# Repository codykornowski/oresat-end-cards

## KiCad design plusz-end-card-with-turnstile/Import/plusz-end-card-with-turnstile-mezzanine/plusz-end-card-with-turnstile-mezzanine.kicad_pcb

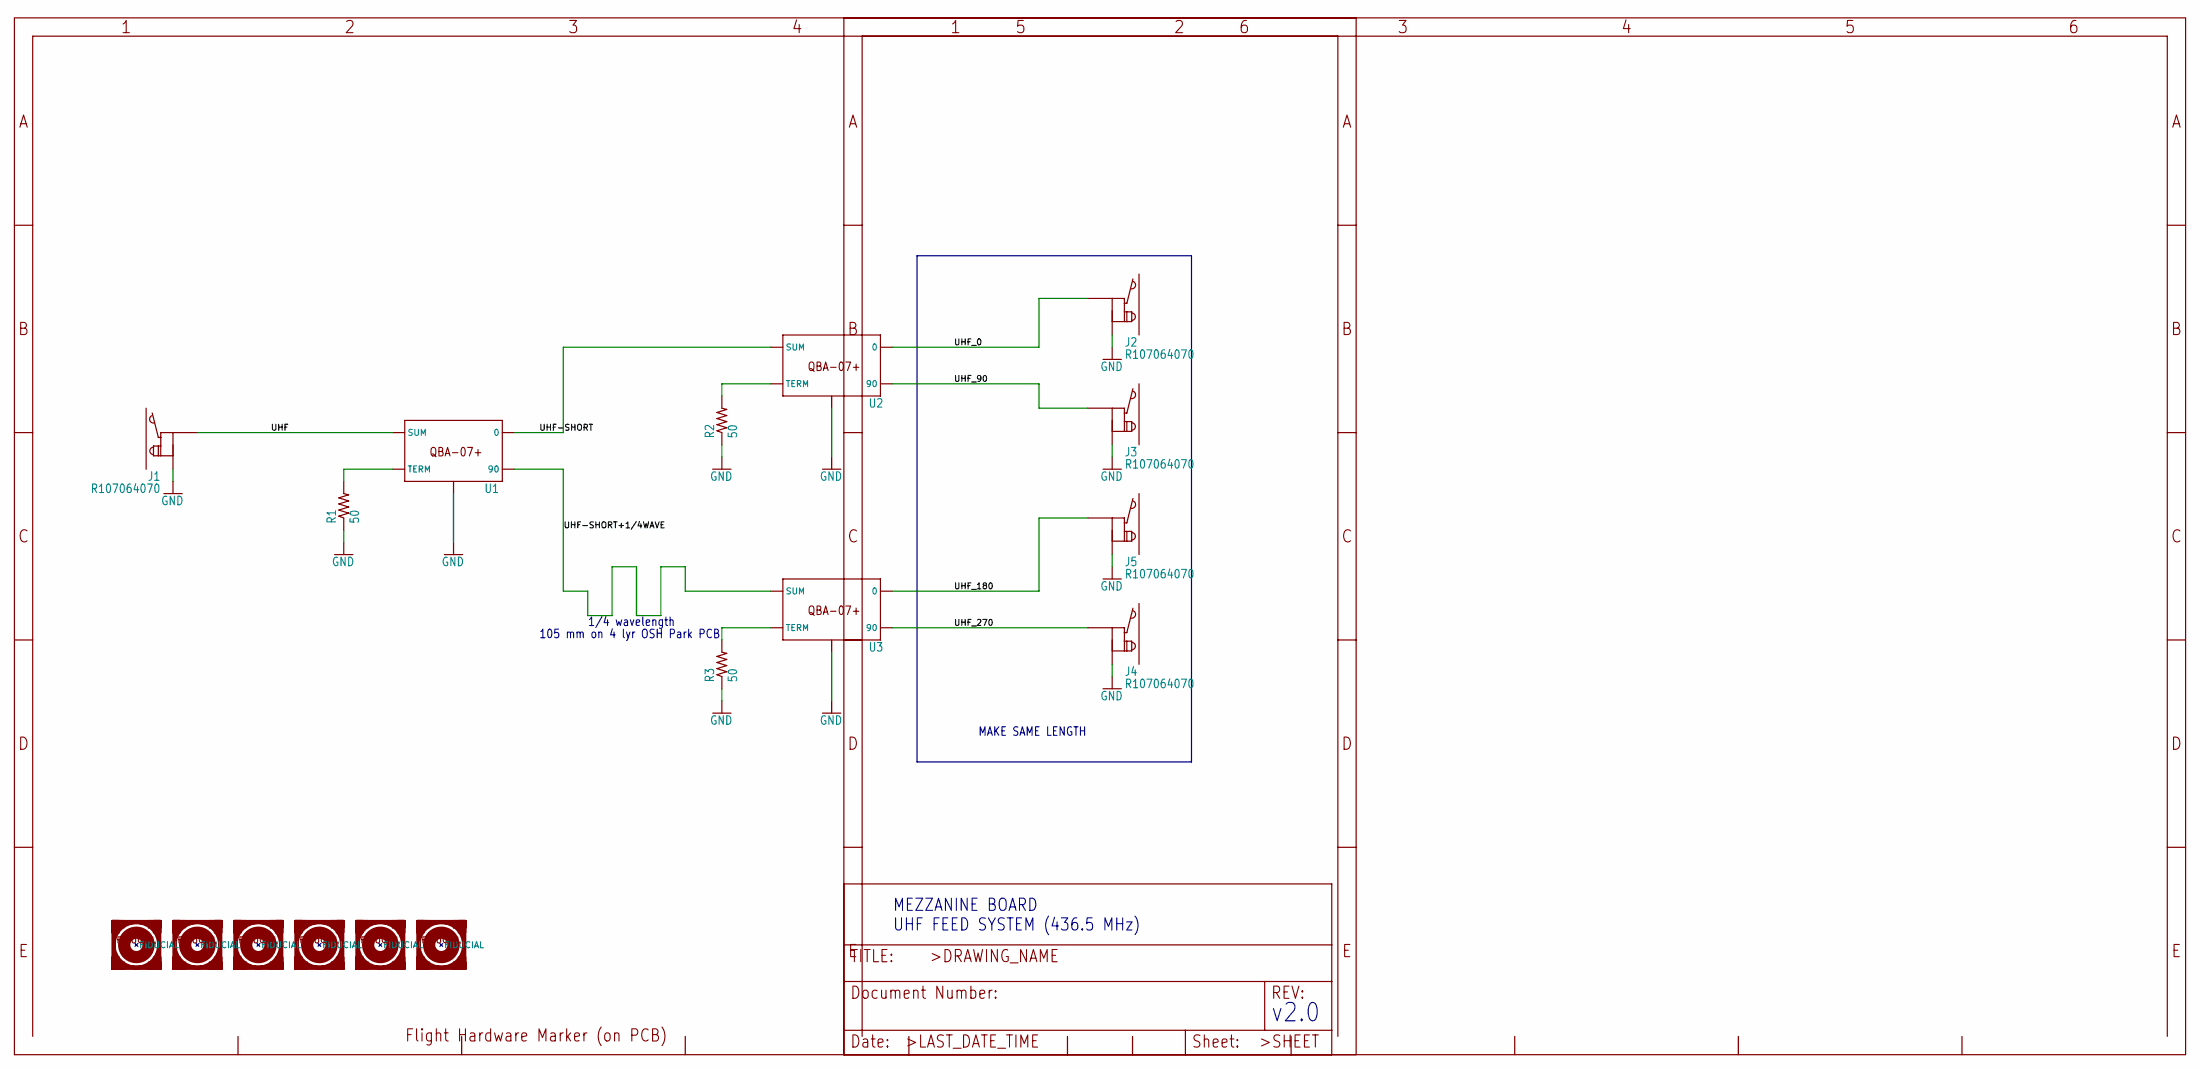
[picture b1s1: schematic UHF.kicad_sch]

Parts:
FIDUCIAL1, FIDUCIAL2, FIDUCIAL3, FIDUCIAL4, FIDUCIAL6, FIDUCIAL7: FIDUCIAL-1.0X2.0
J1, J2, J3, J4, J5: R107064070; R107064070_SOLDER
R1, R2, R3: 50; .0603-C-NOSILK
U1, U2, U3: QBA-07+
U$1: FLIGHMARKERNEW; FLIGHTMARKER_NEW_BOARDS

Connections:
/UHF/UHF: J1.P$1, U1.1 (SUM)
/UHF/UHF-SHORT: U1.6 (0), U2.1 (SUM)
/UHF/UHF-SHORT+1/4WAVE: U1.10 (90), U3.1 (SUM)
/UHF/UHF_0: J2.P$1, U2.6 (0)
/UHF/UHF_90: J3.P$1, U2.10 (90)
/UHF/UHF_180: J5.P$1, U3.6 (0)
/UHF/UHF_270: J4.P$1, U3.10 (90)
GND: J1.P$2, J1.P$3, J2.P$2, J2.P$3, J3.P$2, J3.P$3, J4.P$2, J4.P$3, J5.P$2, J5.P$3, R1.1, R2.1, R3.1, U1.2 (GND), U1.3 (GND), U1.4 (GND), U1.7 (GND), U1.8 (GND), U1.9 (GND), U1.GND-NO-PAD (GND), U2.2 (GND), U2.3 (GND), U2.4 (GND), U2.7 (GND), U2.8 (GND), U2.9 (GND), U2.GND-NO-PAD (GND), U3.2 (GND), U3.3 (GND), U3.4 (GND), U3.7 (GND), U3.8 (GND), U3.9 (GND), U3.GND-NO-PAD (GND); also elsewhere on the board
unnamed: R1.2, U1.5 (TERM)
unnamed: R2.2, U2.5 (TERM)
unnamed: R3.2, U3.5 (TERM)

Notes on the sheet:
MAKE SAME LENGTH
105 mm on 4 lyr OSH Park PCB
v2.0
MEZZANINE BOARD UHF FEED SYSTEM (436.5 MHz)
1/4 wavelength

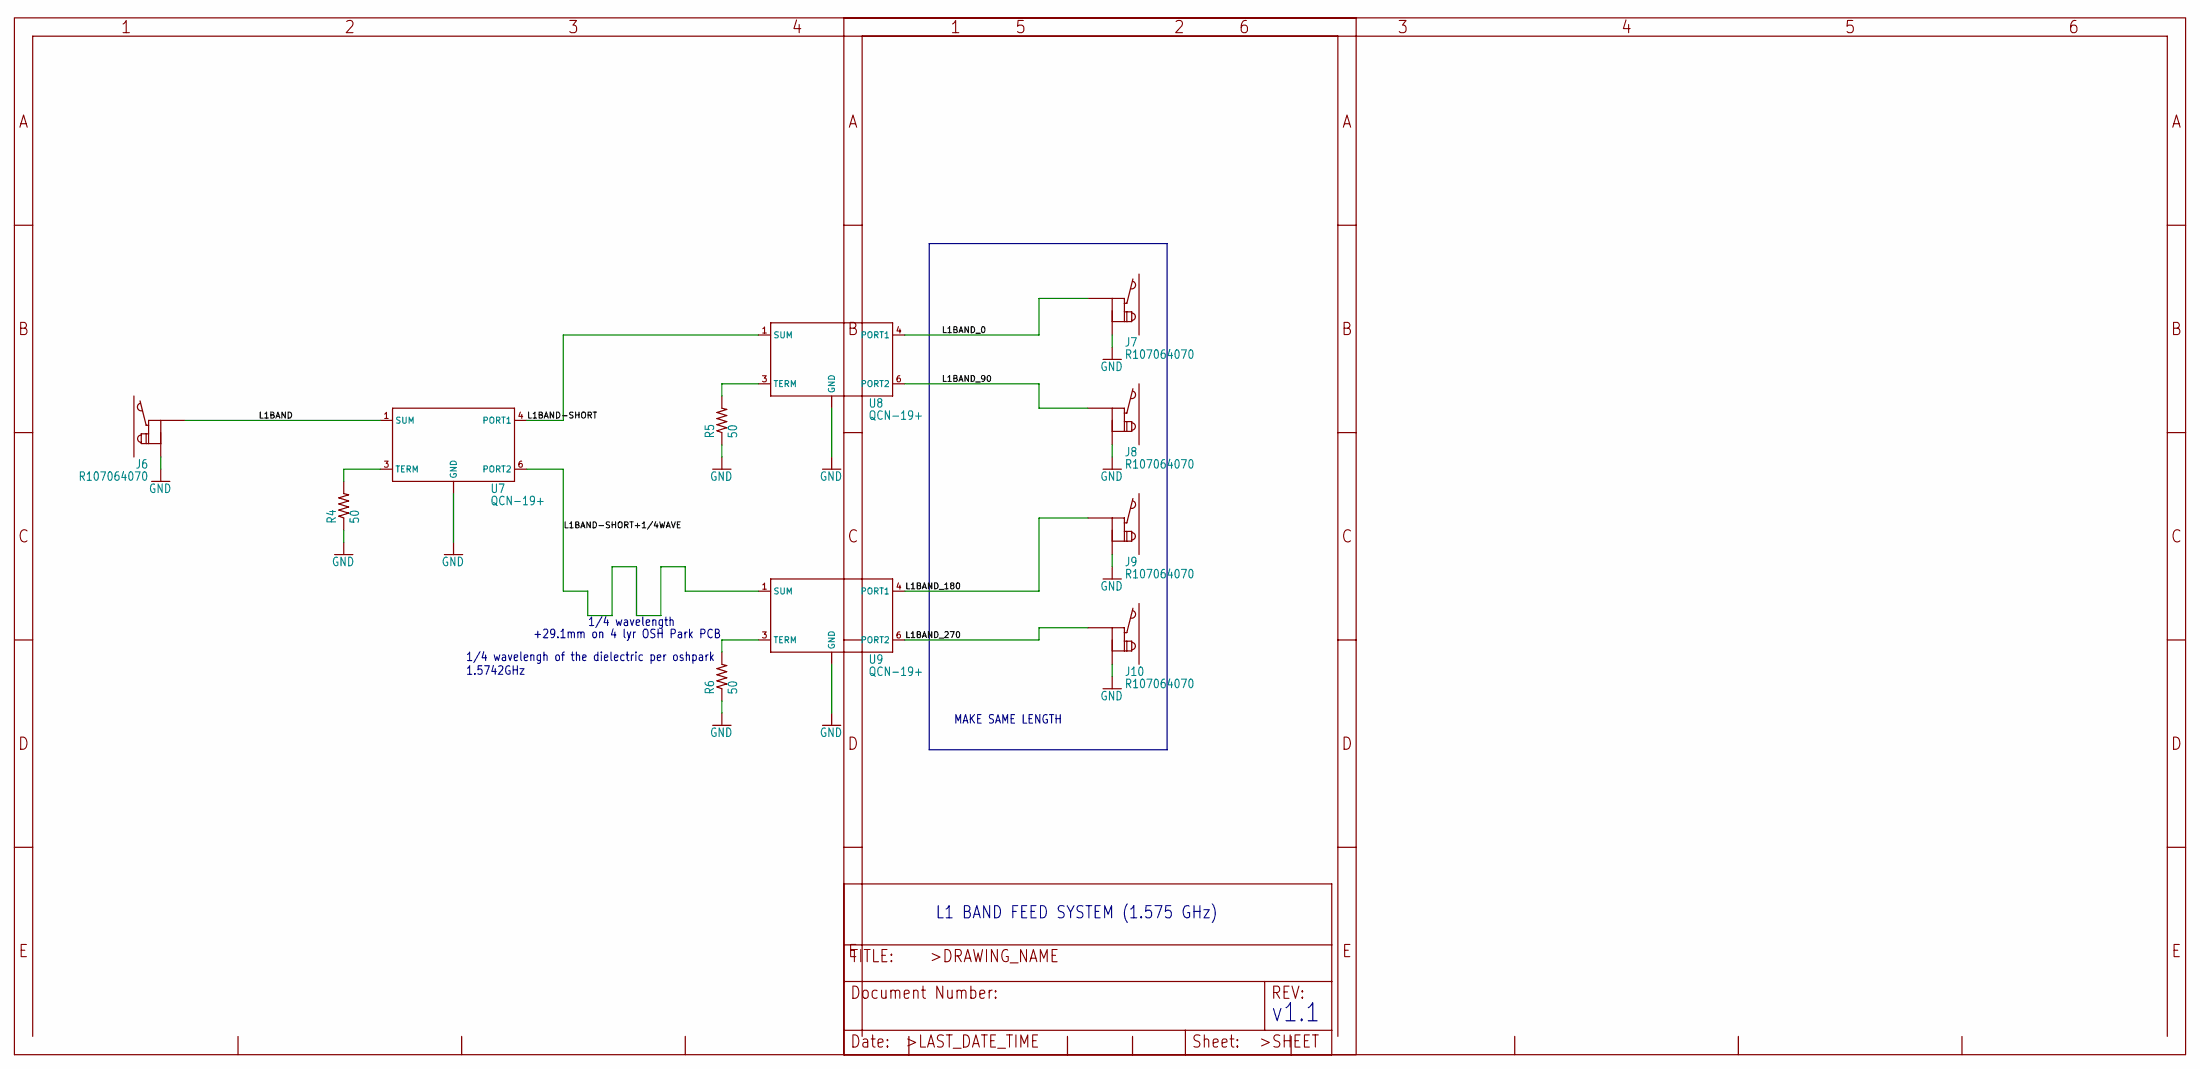
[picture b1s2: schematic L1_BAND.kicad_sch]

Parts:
J6, J7, J8, J9, J10: R107064070; R107064070_SOLDER
R4, R5, R6: 50; .0603-C-NOSILK
U7, U8, U9: QCN-19+; QCN-XXX+

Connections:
/L1 BAND/L1BAND: J6.P$1, U7.1 (SUM)
/L1 BAND/L1BAND-SHORT: U7.4 (PORT1), U8.1 (SUM)
/L1 BAND/L1BAND-SHORT+1/4WAVE: U7.6 (PORT2), U9.1 (SUM)
/L1 BAND/L1BAND_0: J7.P$1, U8.4 (PORT1)
/L1 BAND/L1BAND_90: J8.P$1, U8.6 (PORT2)
/L1 BAND/L1BAND_180: J9.P$1, U9.4 (PORT1)
/L1 BAND/L1BAND_270: J10.P$1, U9.6 (PORT2)
GND: J6.P$2, J6.P$3, J7.P$2, J7.P$3, J8.P$2, J8.P$3, J9.P$2, J9.P$3, J10.P$2, J10.P$3, R4.1, R5.1, R6.1, U7.2 (GND), U7.5 (GND), U8.2 (GND), U8.5 (GND), U9.2 (GND), U9.5 (GND); also elsewhere on the board
unnamed: R4.2, U7.3 (TERM)
unnamed: R5.2, U8.3 (TERM)
unnamed: R6.2, U9.3 (TERM)

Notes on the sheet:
1/4 wavelengh of the dielectric per oshpark 1.5742GHz
L1 BAND FEED SYSTEM (1.575 GHz)
MAKE SAME LENGTH
+29.1mm on 4 lyr OSH Park PCB
v1.1
1/4 wavelength

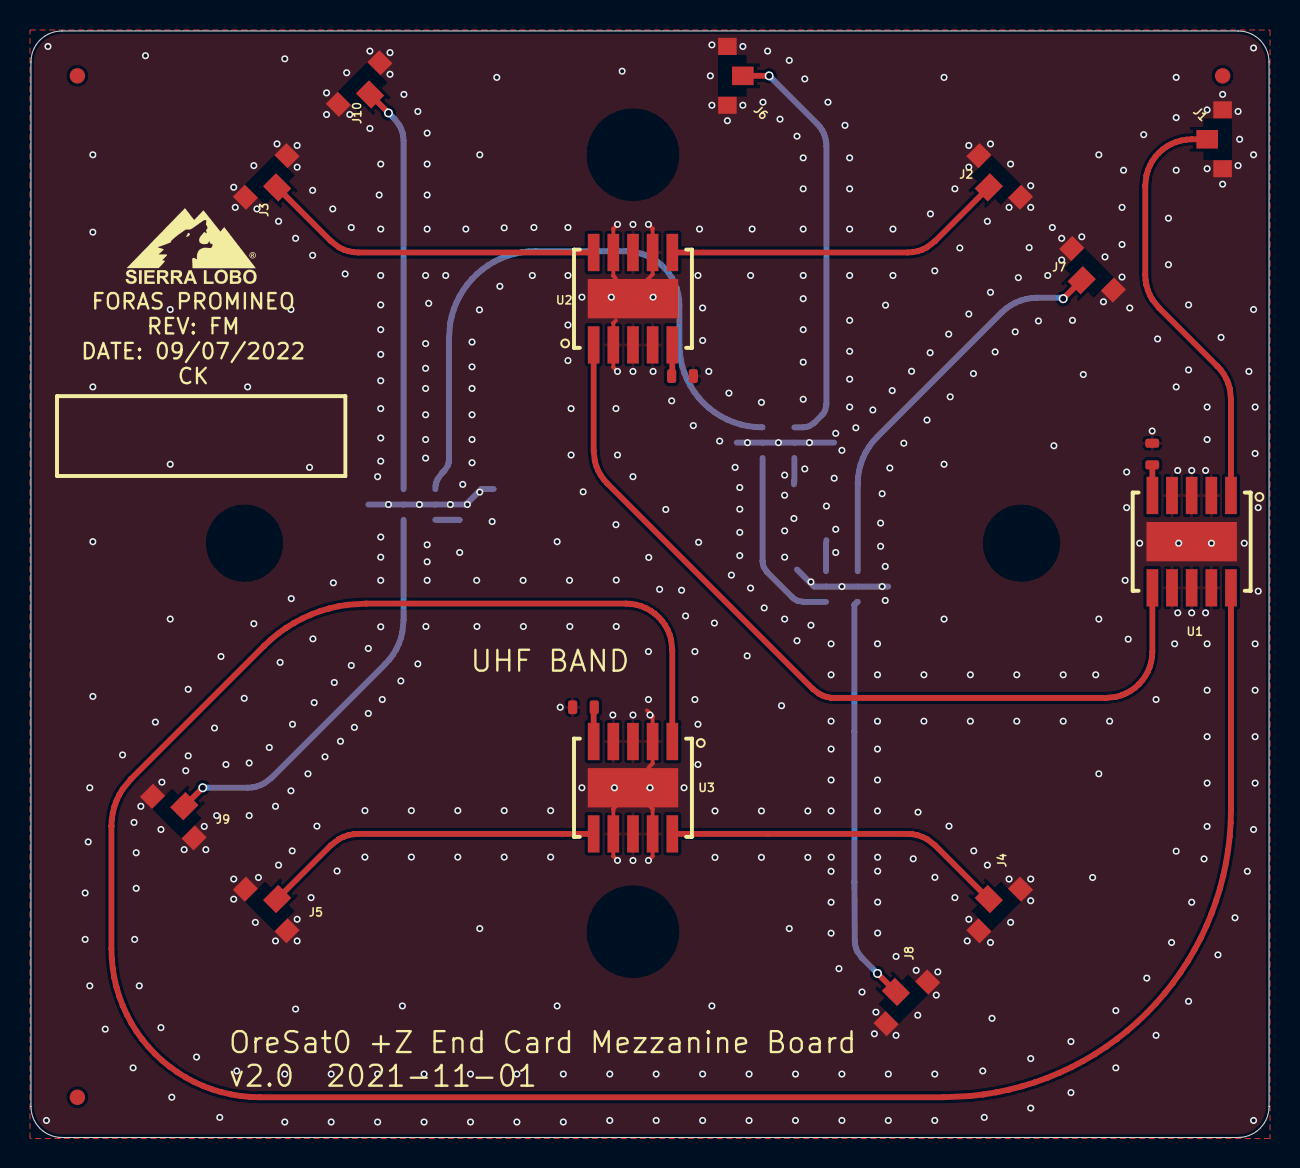
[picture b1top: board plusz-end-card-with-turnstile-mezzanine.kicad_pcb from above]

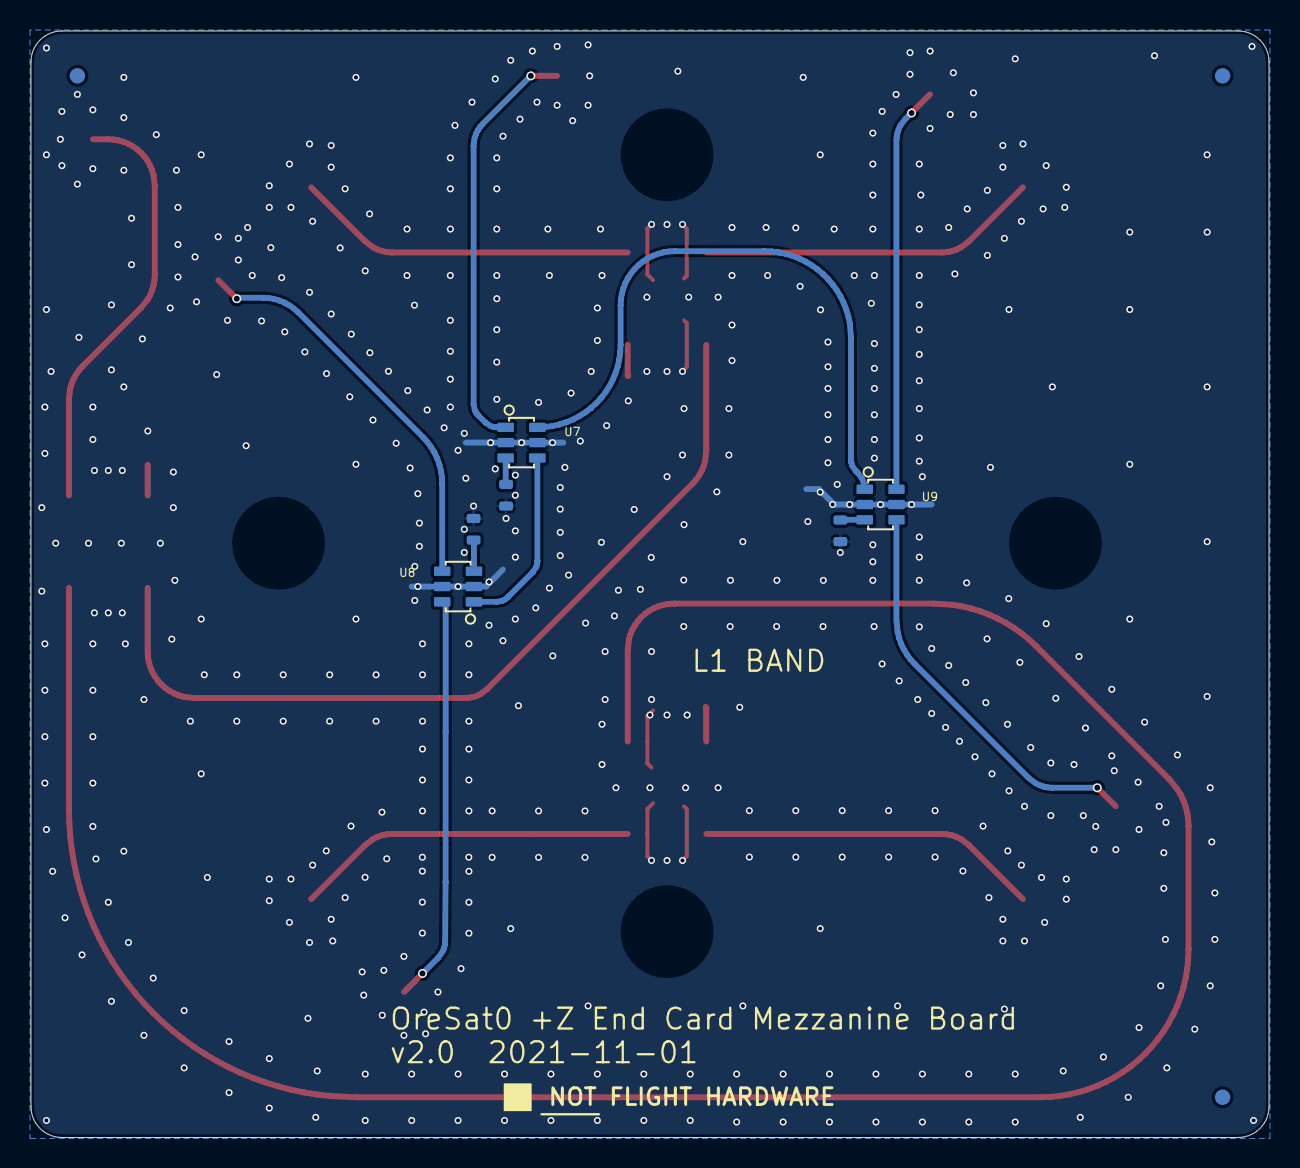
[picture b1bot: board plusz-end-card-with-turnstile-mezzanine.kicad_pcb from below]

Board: 4 copper layers, 80.0 x 71.5 mm, 29 parts (10 on the bottom side), 21 nets.

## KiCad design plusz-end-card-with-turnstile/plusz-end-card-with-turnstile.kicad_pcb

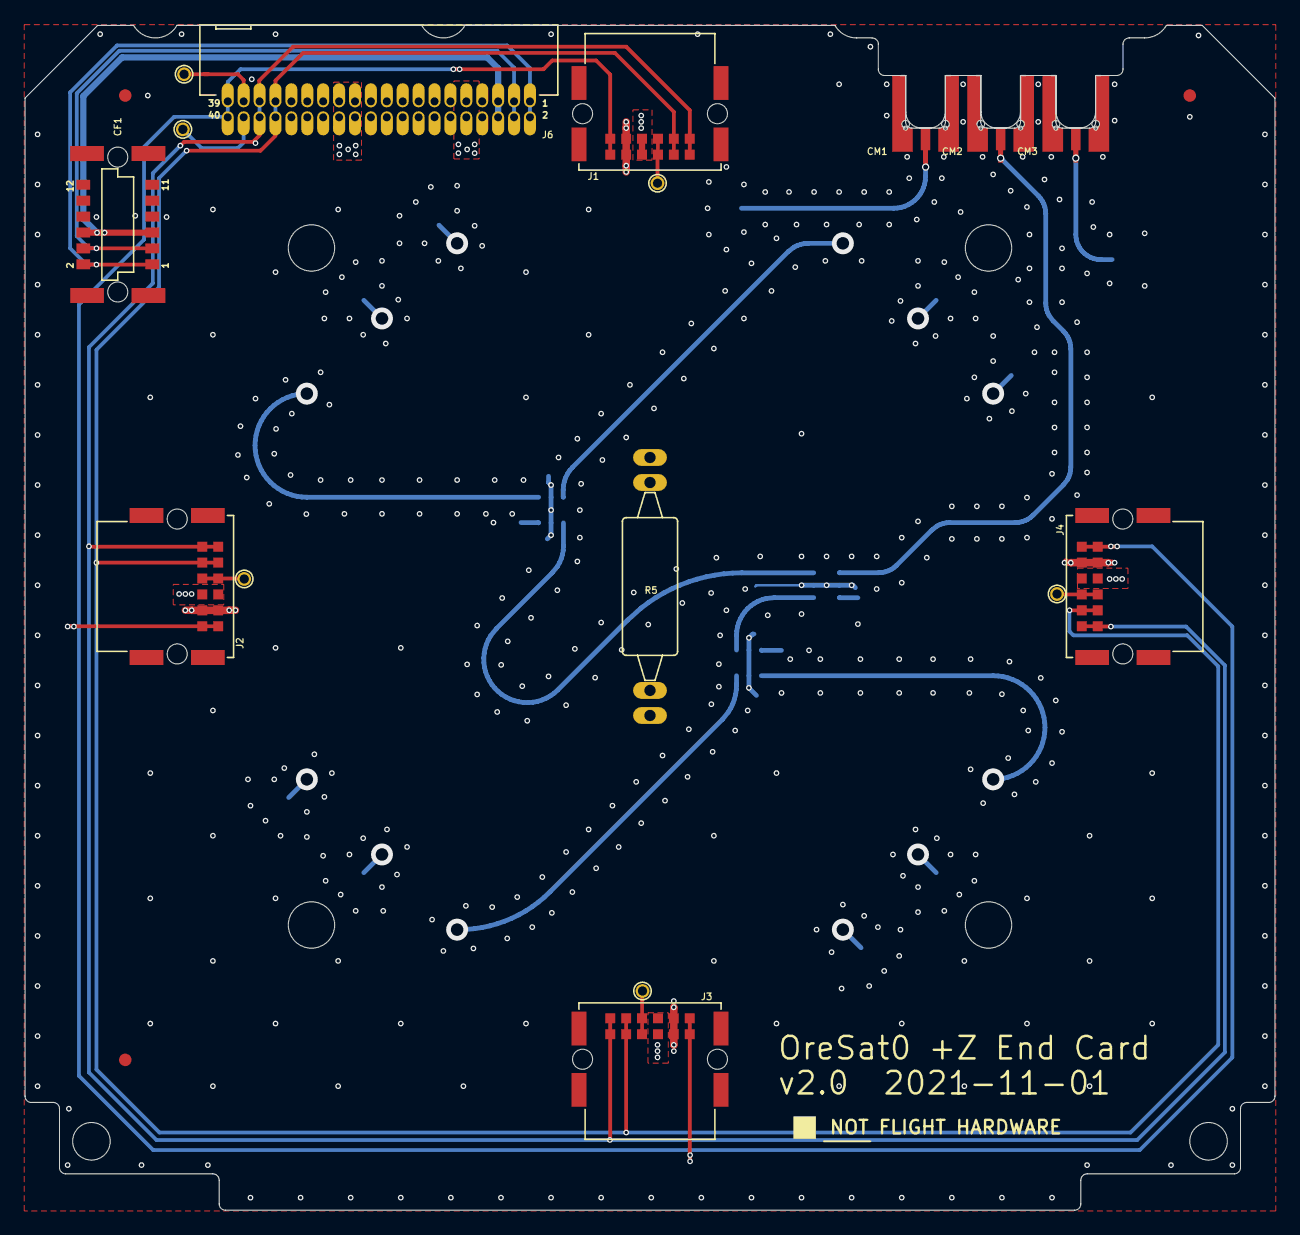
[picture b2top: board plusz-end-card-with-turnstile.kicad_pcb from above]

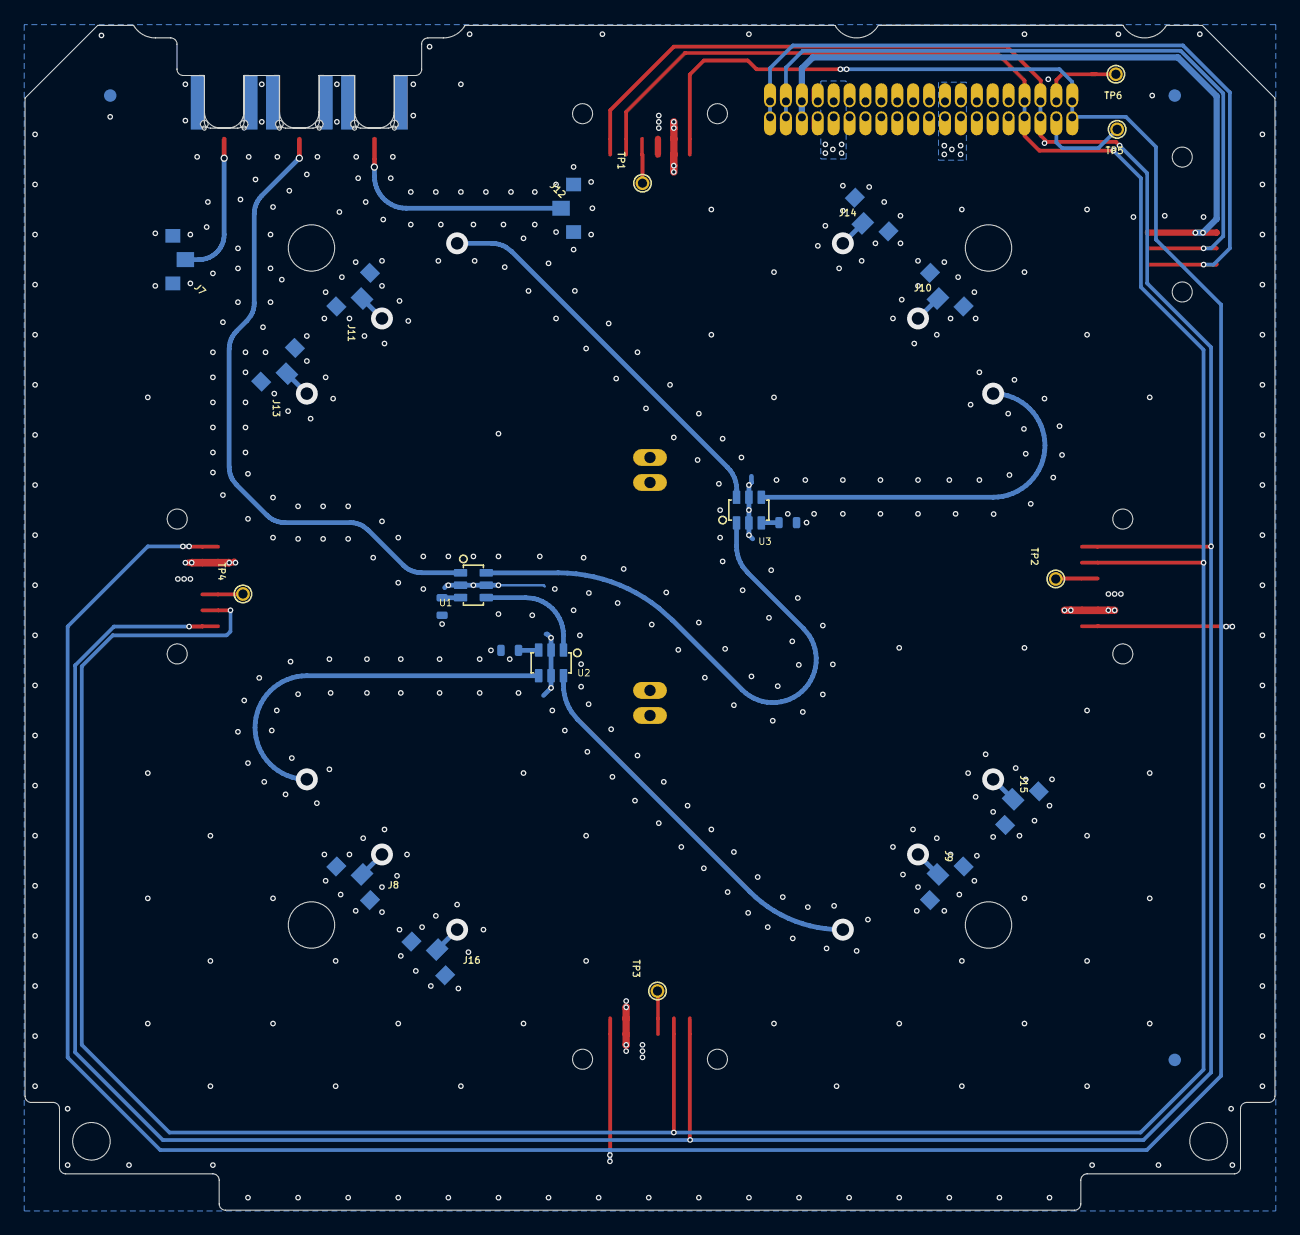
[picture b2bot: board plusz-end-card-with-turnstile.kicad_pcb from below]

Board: 4 copper layers, 99.8 x 94.6 mm, 44 parts (19 on the bottom side), 20 nets.

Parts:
CF1: J-HARWIN-M55-6001242R; HARWIN-M55-60X1242R
CM1, CM2, CM3: J-MOLEX-SMPM-73300-003X; J-MOLEX-SMPM-073300-003X
FIDUCIAL1, FIDUCIAL2, FIDUCIAL3, FIDUCIAL4, FIDUCIAL5, FIDUCIAL6: FIDUCIAL-1.0X2.0
HW1, HW2, HW3, HW4: MCMASTER-94100A150
J1, J2, J3, J4: Harwin M55-7101242R; M55-7101242R
J6: J-SAMTEC-TFM-120-X1-XXX-D-RA
J7, J8, J9, J10, J11, J12, J13, J14, J15, J16: R107064070_CONTACT; R107064070_SOLDER
PCB1: ORESAT-CARD-V1.3-GENERIC-3RF
R1, R2, R3: 50; .0603-C-NOSILK
R5: 7.5 1W; PAC100-FOR-MELTWIRE
TP1, TP2, TP3, TP4, TP5, TP6: TEST-POINT-LARGE-SQUARE; 1X01
U1, U2, U3: QCN-19+; QCN-XXX+
U$1: FLIGHMARKERNEW; FLIGHTMARKER_NEW_BOARDS

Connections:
/CONNECTORS/C3-UART-RX: J6.38, TP5.1
/CONNECTORS/C3-UART-TX: J6.37, TP6.1
/CONNECTORS/CAN1_H: J1.9 (CANH), J1.10 (CANH), J2.9 (CANH), J2.10 (CANH), J3.9 (CANH), J3.10 (CANH), J4.9 (CANH), J4.10 (CANH), J6.33, J6.34
/CONNECTORS/CAN1_L: J1.11 (CANL), J1.12 (CANL), J2.11 (CANL), J2.12 (CANL), J3.11 (CANL), J3.12 (CANL), J4.11 (CANL), J4.12 (CANL), J6.35, J6.36
/CONNECTORS/MAG-POWER: CF1.5, CF1.6, J6.5, J6.6
/CONNECTORS/MAG-SCL: CF1.3, CF1.4, J6.3, J6.4
/CONNECTORS/MAG-SDA: CF1.1, CF1.2, J6.1, J6.2
/CONNECTORS/TURNSTILE-DEPLOY: J6.9, J6.10, R5.P$3 (2), R5.P$4 (2)
/CONNECTORS/VBUS: J1.5 (VBUS), J1.6 (VBUS), J2.5 (VBUS), J2.6 (VBUS), J3.5 (VBUS), J3.6 (VBUS), J4.5 (VBUS), J4.6 (VBUS), J6.23, J6.24, J6.25, J6.26
/CONNECTORS/~SD: J1.1 (~SD), J1.2 (~SD), J2.1 (~SD), J2.2 (~SD), J3.1 (~SD), J3.2 (~SD), J4.1 (~SD), J4.2 (~SD), J6.39, J6.40
/L BAND/LBAND-1/4L: U1.6 (PORT2), U3.1 (SUM)
/L BAND/LBAND-SHORT: U1.4 (PORT1), U2.1 (SUM)
GND: CF1.7, CF1.8, CF1.P$1 (SHIELDS), CF1.P$2 (SHIELDS), CF1.P$3 (SHIELDS), CF1.P$4 (SHIELDS), J1.3 (GND), J1.4 (GND), J1.P$1 (SHIELD), J1.P$2 (SHIELD), J1.P$3 (SHIELD), J1.P$4 (SHIELD), J2.3 (GND), J2.4 (GND), J2.P$1 (SHIELD), J2.P$2 (SHIELD), J2.P$3 (SHIELD), J2.P$4 (SHIELD), J3.3 (GND), J3.4 (GND), J3.P$1 (SHIELD), J3.P$2 (SHIELD), J3.P$3 (SHIELD), J3.P$4 (SHIELD), J4.3 (GND), J4.4 (GND), J4.P$1 (SHIELD), J4.P$2 (SHIELD), J4.P$3 (SHIELD), J4.P$4 (SHIELD), J6.27, J6.28, J6.29, J6.30, J7.P$2, J7.P$3, J8.P$2, J8.P$3, J9.P$2, J9.P$3, J10.P$2, J10.P$3, J11.P$2, J11.P$3, J12.P$2, J12.P$3, J13.P$2, J13.P$3, J14.P$2, J14.P$3, J15.P$2, J15.P$3, J16.P$2, J16.P$3, R1.1, R2.1, R3.1, R5.P$1 (1), R5.P$2 (1), U1.2 (GND), U1.5 (GND), U2.2 (GND), U2.5 (GND), U3.2 (GND), U3.5 (GND)
unnamed: J1.7 (AUX), J1.8 (AUX), TP1.1
unnamed: J2.7 (AUX), J2.8 (AUX), TP2.1
unnamed: J3.7 (AUX), J3.8 (AUX), TP3.1
unnamed: J4.7 (AUX), J4.8 (AUX), TP4.1
unnamed: R1.2, U1.3 (TERM)
unnamed: R2.2, U2.3 (TERM)
unnamed: R3.2, U3.3 (TERM)

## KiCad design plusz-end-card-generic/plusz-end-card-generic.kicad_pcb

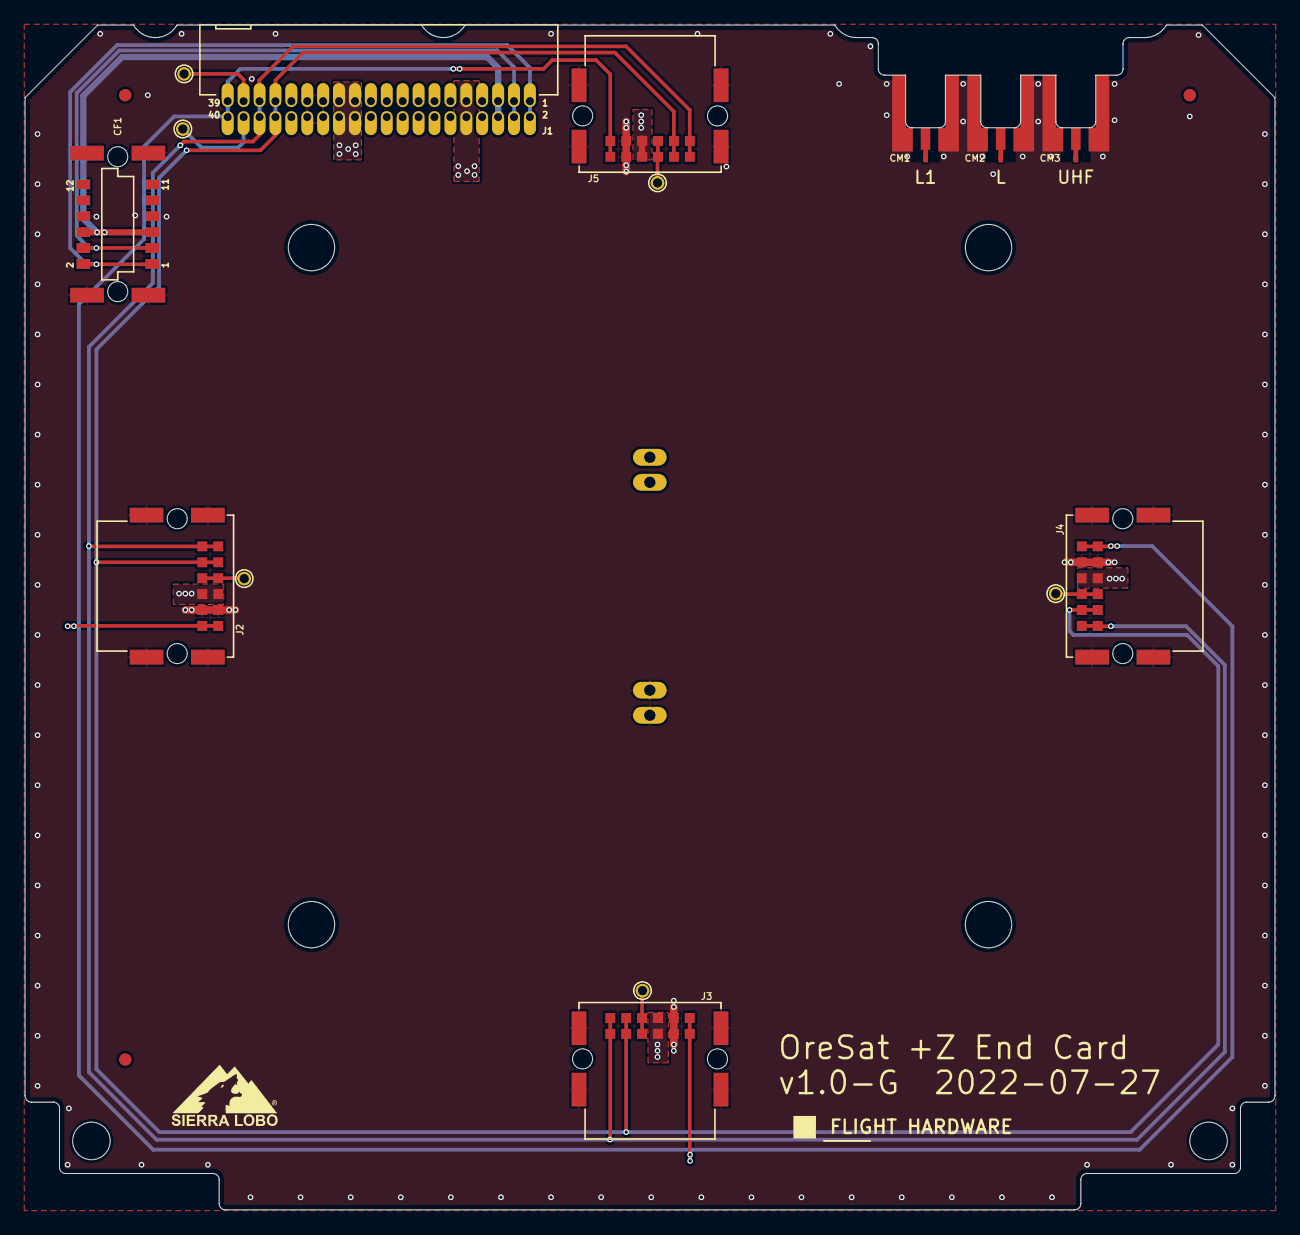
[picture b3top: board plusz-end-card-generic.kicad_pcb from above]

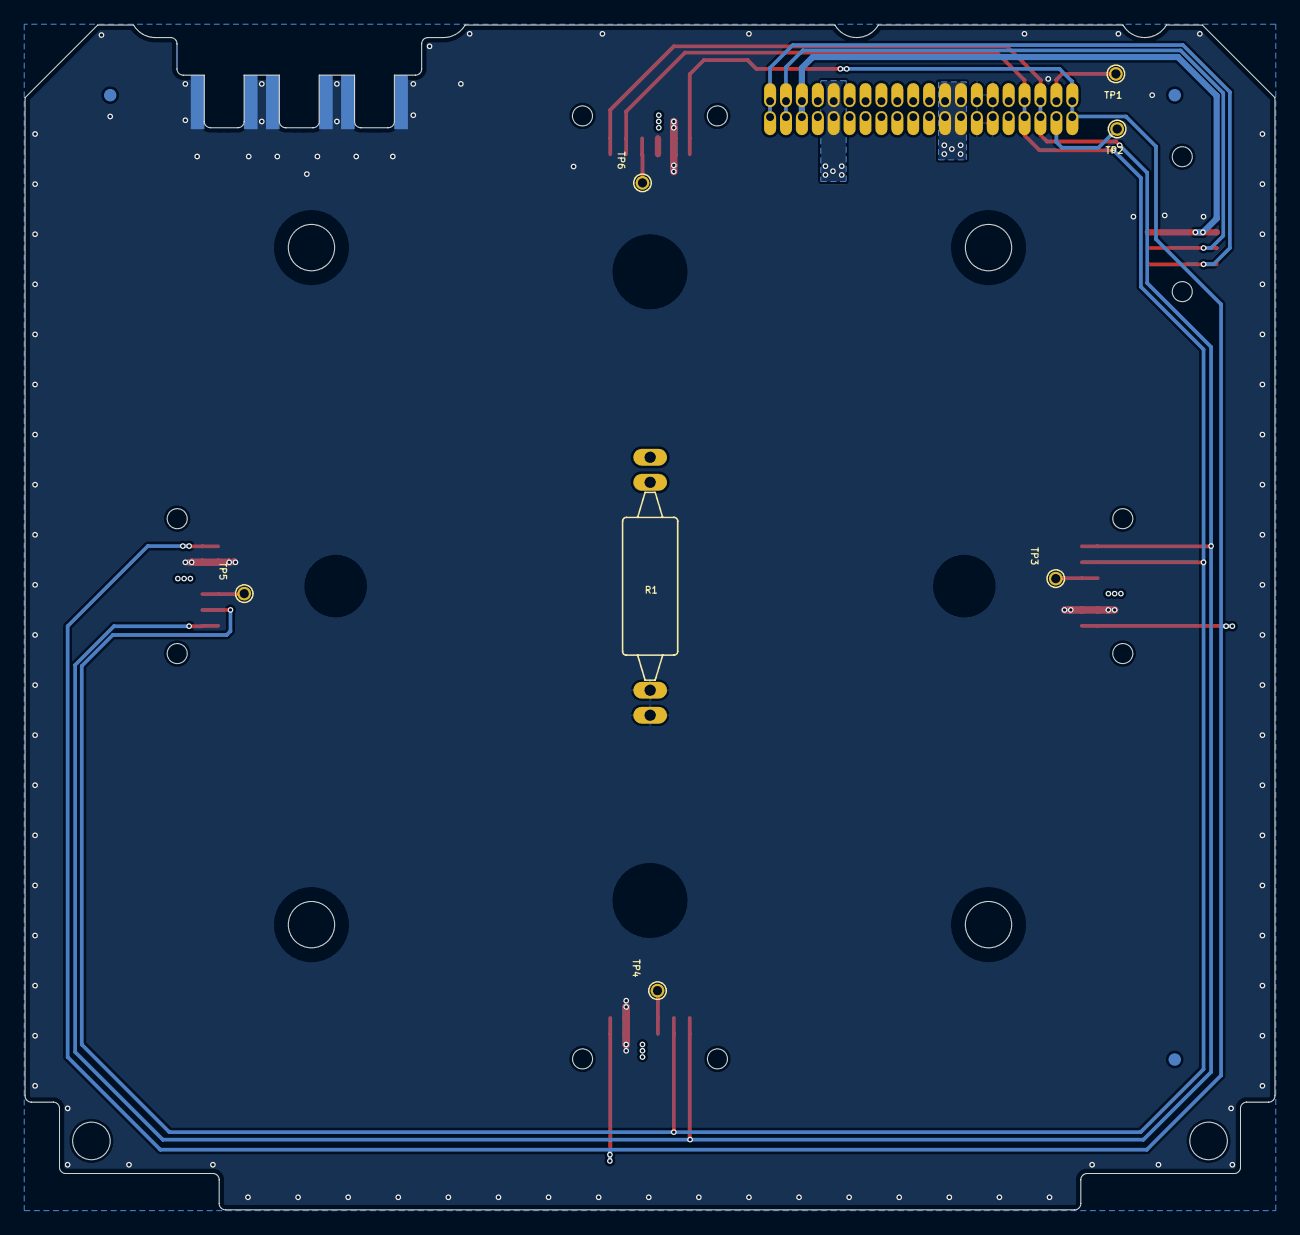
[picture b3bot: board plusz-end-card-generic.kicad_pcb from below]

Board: 4 copper layers, 99.8 x 94.6 mm, 28 parts (4 on the bottom side), 15 nets.

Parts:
CF1: J-HARWIN-M55-6001242R; HARWIN-M55-60X1242R
CM1, CM2, CM3: J-MOLEX-SMPM-73300-003X; J-MOLEX-SMPM-073300-003X
FIDUCIAL1, FIDUCIAL2, FIDUCIAL3, FIDUCIAL4, FIDUCIAL5, FIDUCIAL6: FIDUCIAL-1.0X2.0
HW1, HW2, HW3, HW4: MCMASTER-94100A150; H-MCMASTER-94100A150
J1: J-SAMTEC-TFM-120-X1-XXX-D-RA
J2, J3, J4, J5: Harwin M55-7101242R; J-Harwin-M55-7101242R
PCB1: ORESAT-CARD-V1.3-GENERIC-3RF
R1: 7.5 1W; R-PAC100-FOR-MELTWIRE
TP1, TP2, TP3, TP4, TP5, TP6: TEST-POINT-LARGE-SQUARE; 1X01
U$1: FLIGHMARKERNEW; FLIGHTMARKER_NEW_BOARDS

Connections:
/CONNECTORS/C3-UART-RX: J1.38, TP2.1
/CONNECTORS/C3-UART-TX: J1.37, TP1.1
/CONNECTORS/CAN1_H: J1.33, J1.34, J2.9 (CANH), J2.10 (CANH), J3.9 (CANH), J3.10 (CANH), J4.9 (CANH), J4.10 (CANH), J5.9 (CANH), J5.10 (CANH)
/CONNECTORS/CAN1_L: J1.35, J1.36, J2.11 (CANL), J2.12 (CANL), J3.11 (CANL), J3.12 (CANL), J4.11 (CANL), J4.12 (CANL), J5.11 (CANL), J5.12 (CANL)
/CONNECTORS/MAG-POWER: CF1.5, CF1.6, J1.5, J1.6
/CONNECTORS/MAG-SCL: CF1.3, CF1.4, J1.3, J1.4
/CONNECTORS/MAG-SDA: CF1.1, CF1.2, J1.1, J1.2
/CONNECTORS/TURNSTILE-DEPLOY: J1.9, J1.10, R1.P$3 (2), R1.P$4 (2)
/CONNECTORS/VBUS: J1.23, J1.24, J1.25, J1.26, J2.5 (VBUS), J2.6 (VBUS), J3.5 (VBUS), J3.6 (VBUS), J4.5 (VBUS), J4.6 (VBUS), J5.5 (VBUS), J5.6 (VBUS)
/CONNECTORS/~SD: J1.39, J1.40, J2.1 (~SD), J2.2 (~SD), J3.1 (~SD), J3.2 (~SD), J4.1 (~SD), J4.2 (~SD), J5.1 (~SD), J5.2 (~SD)
GND: CF1.7, CF1.8, CF1.P$1 (SHIELDS), CF1.P$2 (SHIELDS), CF1.P$3 (SHIELDS), CF1.P$4 (SHIELDS), CM1.GND (SHIELD3), CM2.GND (SHIELD3), CM3.GND (SHIELD3), J1.27, J1.28, J1.29, J1.30, J2.3 (GND), J2.4 (GND), J2.GND (SHIELD), J3.3 (GND), J3.4 (GND), J3.GND (SHIELD), J4.3 (GND), J4.4 (GND), J4.GND (SHIELD), J5.3 (GND), J5.4 (GND), J5.GND (SHIELD), R1.P$1 (1), R1.P$2 (1)
unnamed: J2.7 (AUX), J2.8 (AUX), TP3.1
unnamed: J3.7 (AUX), J3.8 (AUX), TP4.1
unnamed: J4.7 (AUX), J4.8 (AUX), TP5.1
unnamed: J5.7 (AUX), J5.8 (AUX), TP6.1
